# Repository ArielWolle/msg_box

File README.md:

# msg_box

This project is for couples who want to send cute messages at the push of a button. It is loosely inspired by the bond touch bracelet (https://www.bond-touch.com/), but instad of just vibration it has an 8x8 neopixel array as well as vibration.

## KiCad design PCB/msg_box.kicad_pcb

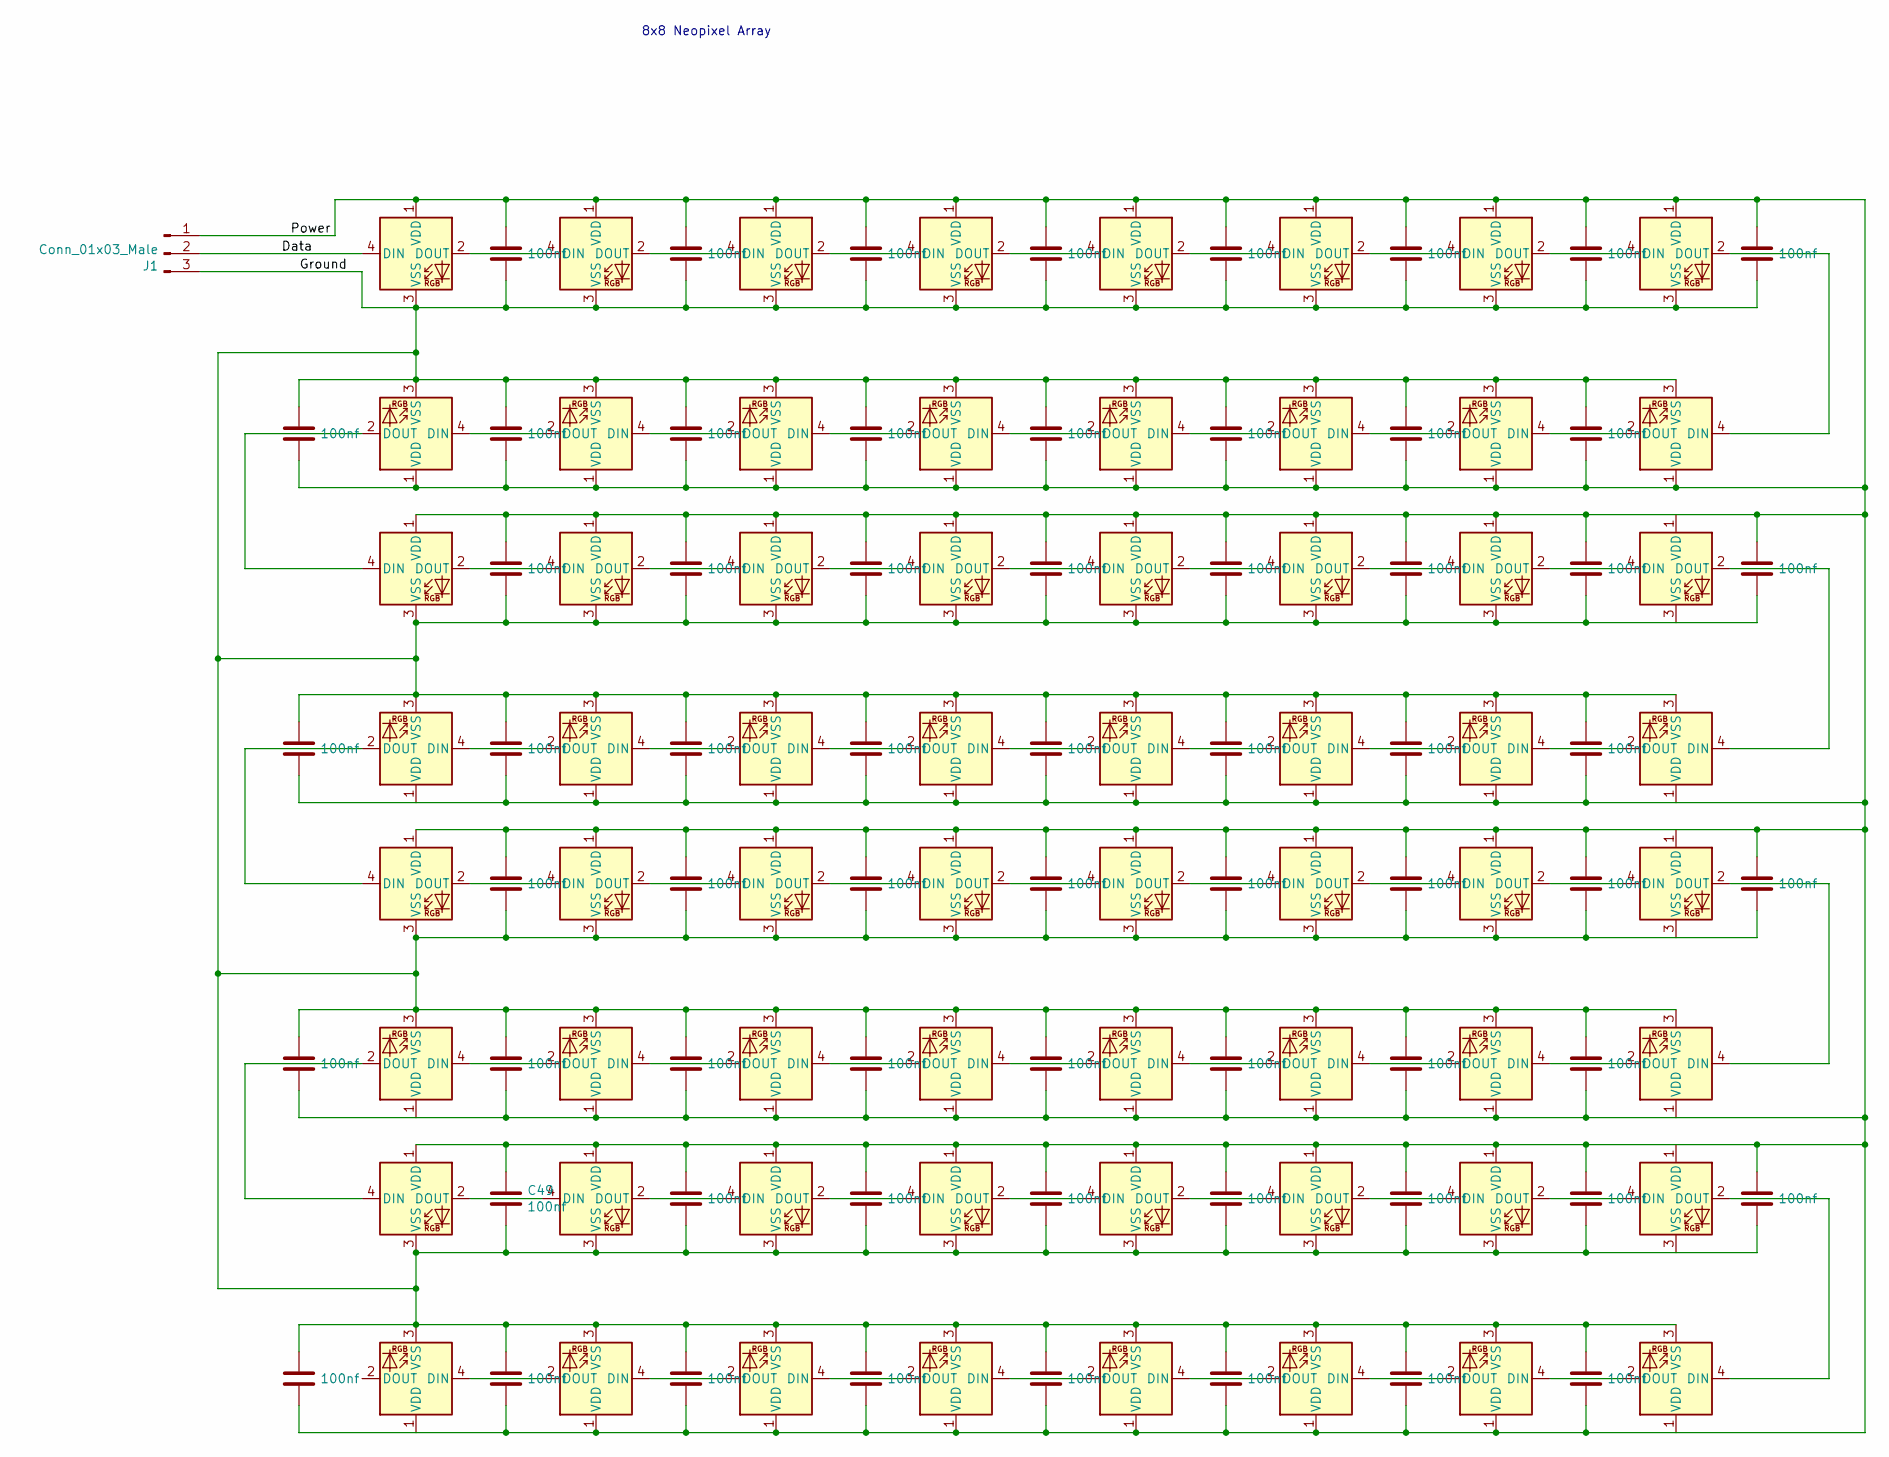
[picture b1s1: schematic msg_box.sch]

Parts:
C1, C2, C3, C4, C5, C6, C7, C8, C9, C10, C11, C12, C13, C14, C15, C16, C17, C18, C19, C20, C21, C22, C23, C24, C25, C26, C27, C28, C29, C30, C31, C32, C33, C34, C35, C36, C37, C38, C39, C40, C41, C42, C43, C44, C45, C46, C47, C48, C49, C50, C51, C52, C53, C54, C55, C56, C57, C58, C59, C60, C61, C62, C63, C64: 100nf; C_0805_2012Metric_Pad1.18x1.45mm_HandSolder
D1, D2, D3, D4, D5, D6, D7, D8, D9, D10, D11, D12, D13, D14, D15, D16, D17, D18, D19, D20, D21, D22, D23, D24, D25, D26, D27, D28, D29, D30, D31, D32, D33, D34, D35, D36, D37, D38, D39, D40, D41, D42, D43, D44, D45, D46, D47, D48, D49, D50, D51, D52, D53, D54, D55, D56, D57, D58, D59, D60, D61, D62, D63, D64: WS2812B; LED_WS2812B_PLCC4_5.0x5.0mm_P3.2mm
J1: Conn_01x03_Male; PinHeader_1x03_P2.54mm_Vertical

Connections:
/Data: D1.4 (DIN), J1.2
/Ground: C1.2, C2.2, C3.2, C4.2, C5.2, C6.2, C7.2, C8.2, C9.1, C10.1, C11.1, C12.1, C13.1, C14.1, C15.1, C16.1, C17.2, C18.2, C19.2, C20.2, C21.2, C22.2, C23.2, C24.2, C25.1, C26.1, C27.1, C28.1, C29.1, C30.1, C31.1, C32.1, C33.2, C34.2, C35.2, C36.2, C37.2, C38.2, C39.2, C40.2, C41.1, C42.1, C43.1, C44.1, C45.1, C46.1, C47.1, C48.1, C49.2, C50.2, C51.2, C52.2, C53.2, C54.2, C55.2, C56.2, C57.1, C58.1, C59.1, C60.1, C61.1, C62.1, C63.1, C64.1, D1.3 (VSS), D2.3 (VSS), D3.3 (VSS), D4.3 (VSS), D5.3 (VSS), D6.3 (VSS), D7.3 (VSS), D8.3 (VSS), D9.3 (VSS), D10.3 (VSS), D11.3 (VSS), D12.3 (VSS), D13.3 (VSS), D14.3 (VSS), D15.3 (VSS), D16.3 (VSS), D17.3 (VSS), D18.3 (VSS), D19.3 (VSS), D20.3 (VSS), D21.3 (VSS), D22.3 (VSS), D23.3 (VSS), D24.3 (VSS), D25.3 (VSS), D26.3 (VSS), D27.3 (VSS), D28.3 (VSS), D29.3 (VSS), D30.3 (VSS), D31.3 (VSS), D32.3 (VSS), D33.3 (VSS), D34.3 (VSS), D35.3 (VSS), D36.3 (VSS), D37.3 (VSS), D38.3 (VSS), D39.3 (VSS), D40.3 (VSS), D41.3 (VSS), D42.3 (VSS), D43.3 (VSS), D44.3 (VSS), D45.3 (VSS), D46.3 (VSS), D47.3 (VSS), D48.3 (VSS), D49.3 (VSS), D50.3 (VSS), D51.3 (VSS), D52.3 (VSS), D53.3 (VSS), D54.3 (VSS), D55.3 (VSS), D56.3 (VSS), D57.3 (VSS), D58.3 (VSS), D59.3 (VSS), D60.3 (VSS), D61.3 (VSS), D62.3 (VSS), D63.3 (VSS), D64.3 (VSS), J1.3
/Power: C1.1, C2.1, C3.1, C4.1, C5.1, C6.1, C7.1, C8.1, C9.2, C10.2, C11.2, C12.2, C13.2, C14.2, C15.2, C16.2, C17.1, C18.1, C19.1, C20.1, C21.1, C22.1, C23.1, C24.1, C25.2, C26.2, C27.2, C28.2, C29.2, C30.2, C31.2, C32.2, C33.1, C34.1, C35.1, C36.1, C37.1, C38.1, C39.1, C40.1, C41.2, C42.2, C43.2, C44.2, C45.2, C46.2, C47.2, C48.2, C49.1, C50.1, C51.1, C52.1, C53.1, C54.1, C55.1, C56.1, C57.2, C58.2, C59.2, C60.2, C61.2, C62.2, C63.2, C64.2, D1.1 (VDD), D2.1 (VDD), D3.1 (VDD), D4.1 (VDD), D5.1 (VDD), D6.1 (VDD), D7.1 (VDD), D8.1 (VDD), D9.1 (VDD), D10.1 (VDD), D11.1 (VDD), D12.1 (VDD), D13.1 (VDD), D14.1 (VDD), D15.1 (VDD), D16.1 (VDD), D17.1 (VDD), D18.1 (VDD), D19.1 (VDD), D20.1 (VDD), D21.1 (VDD), D22.1 (VDD), D23.1 (VDD), D24.1 (VDD), D25.1 (VDD), D26.1 (VDD), D27.1 (VDD), D28.1 (VDD), D29.1 (VDD), D30.1 (VDD), D31.1 (VDD), D32.1 (VDD), D33.1 (VDD), D34.1 (VDD), D35.1 (VDD), D36.1 (VDD), D37.1 (VDD), D38.1 (VDD), D39.1 (VDD), D40.1 (VDD), D41.1 (VDD), D42.1 (VDD), D43.1 (VDD), D44.1 (VDD), D45.1 (VDD), D46.1 (VDD), D47.1 (VDD), D48.1 (VDD), D49.1 (VDD), D50.1 (VDD), D51.1 (VDD), D52.1 (VDD), D53.1 (VDD), D54.1 (VDD), D55.1 (VDD), D56.1 (VDD), D57.1 (VDD), D58.1 (VDD), D59.1 (VDD), D60.1 (VDD), D61.1 (VDD), D62.1 (VDD), D63.1 (VDD), D64.1 (VDD), J1.1
unnamed: D1.2 (DOUT), D2.4 (DIN)
unnamed: D2.2 (DOUT), D3.4 (DIN)
unnamed: D3.2 (DOUT), D4.4 (DIN)
unnamed: D4.2 (DOUT), D5.4 (DIN)
unnamed: D5.2 (DOUT), D6.4 (DIN)
unnamed: D6.2 (DOUT), D7.4 (DIN)
unnamed: D7.2 (DOUT), D8.4 (DIN)
unnamed: D9.4 (DIN), D10.2 (DOUT)
unnamed: D10.4 (DIN), D11.2 (DOUT)
unnamed: D11.4 (DIN), D12.2 (DOUT)
unnamed: D12.4 (DIN), D13.2 (DOUT)
unnamed: D13.4 (DIN), D14.2 (DOUT)
unnamed: D14.4 (DIN), D15.2 (DOUT)
unnamed: D15.4 (DIN), D16.2 (DOUT)
unnamed: D8.2 (DOUT), D16.4 (DIN)
unnamed: D17.2 (DOUT), D18.4 (DIN)
unnamed: D9.2 (DOUT), D17.4 (DIN)
unnamed: D18.2 (DOUT), D19.4 (DIN)
unnamed: D19.2 (DOUT), D20.4 (DIN)
unnamed: D20.2 (DOUT), D21.4 (DIN)
unnamed: D21.2 (DOUT), D22.4 (DIN)
unnamed: D22.2 (DOUT), D23.4 (DIN)
unnamed: D23.2 (DOUT), D24.4 (DIN)
unnamed: D24.2 (DOUT), D32.4 (DIN)
unnamed: D25.2 (DOUT), D33.4 (DIN)
unnamed: D25.4 (DIN), D26.2 (DOUT)
unnamed: D26.4 (DIN), D27.2 (DOUT)
unnamed: D27.4 (DIN), D28.2 (DOUT)
unnamed: D28.4 (DIN), D29.2 (DOUT)
unnamed: D29.4 (DIN), D30.2 (DOUT)
unnamed: D30.4 (DIN), D31.2 (DOUT)
unnamed: D31.4 (DIN), D32.2 (DOUT)
unnamed: D33.2 (DOUT), D34.4 (DIN)
unnamed: D34.2 (DOUT), D35.4 (DIN)
unnamed: D35.2 (DOUT), D36.4 (DIN)
unnamed: D36.2 (DOUT), D37.4 (DIN)
unnamed: D37.2 (DOUT), D38.4 (DIN)
unnamed: D38.2 (DOUT), D39.4 (DIN)
unnamed: D39.2 (DOUT), D40.4 (DIN)
unnamed: D40.2 (DOUT), D48.4 (DIN)
unnamed: D41.2 (DOUT), D49.4 (DIN)
unnamed: D41.4 (DIN), D42.2 (DOUT)
unnamed: D42.4 (DIN), D43.2 (DOUT)
unnamed: D43.4 (DIN), D44.2 (DOUT)
unnamed: D44.4 (DIN), D45.2 (DOUT)
unnamed: D45.4 (DIN), D46.2 (DOUT)
unnamed: D46.4 (DIN), D47.2 (DOUT)
unnamed: D47.4 (DIN), D48.2 (DOUT)
unnamed: D49.2 (DOUT), D50.4 (DIN)
unnamed: D50.2 (DOUT), D51.4 (DIN)
unnamed: D51.2 (DOUT), D52.4 (DIN)
unnamed: D52.2 (DOUT), D53.4 (DIN)
unnamed: D53.2 (DOUT), D54.4 (DIN)
unnamed: D54.2 (DOUT), D55.4 (DIN)
unnamed: D55.2 (DOUT), D56.4 (DIN)
unnamed: D56.2 (DOUT), D64.4 (DIN)
unnamed: D57.4 (DIN), D58.2 (DOUT)
unnamed: D58.4 (DIN), D59.2 (DOUT)
unnamed: D59.4 (DIN), D60.2 (DOUT)
unnamed: D60.4 (DIN), D61.2 (DOUT)
unnamed: D61.4 (DIN), D62.2 (DOUT)
unnamed: D62.4 (DIN), D63.2 (DOUT)
unnamed: D63.4 (DIN), D64.2 (DOUT)

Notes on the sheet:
8x8 Neopixel Array

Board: 2 copper layers, 129 parts (0 on the bottom side), 66 nets, no tracks yet.

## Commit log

2021-10-14 completed a bsic mqqt server
2021-10-15 added time constraint on button press
2021-10-19 Simplified Server and renamed button inputs file
2021-10-19 Improved server and added text upload feature
2021-10-19 added automatic naming for MQTT topics
2021-10-20 renamed boxes to work with the old system
2021-10-20 renamed MQTT topics to work with legacy system
2021-10-21 Simplified files using imports
2021-10-21 made topic name a variable
2021-10-27 Added esp32 code basics and PCB folder
2021-10-27 Restructered file system
2021-10-27 added PCB files
2021-10-28 enabled multicore support on server
2021-11-02 Allowed Wifi Credentials Change
2021-12-01 completed firmwarre except vibration
2021-12-01 comepleted firmware except vibration
